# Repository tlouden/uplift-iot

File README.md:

# UPLIFT-IoT
Connecting an [UPLIFT](https://www.upliftdesk.com/) desk to Home Assistant using an ESP32 with ESP Home for Home Assistant.

## Disclaimer
This is an adversarial interop against a hardware interface. Any changes from the manufacturer could invalidate or even make this dangerous. Validate assumptions on your own system and proceed with caution. 

## Usage
The UART driver for ESP Home should work without modification. Everything else will need to be customized to your setup using the provided examples.

## ESP Home
An ESP32 is used with [ESP Home](https://esphome.io/). The specific board is a esp32doit-devkit-v1.
### esphome/uplift_uart.h
Custom UART driver that interprets the data from the UPLift desk unit.
### uplift-iot.yaml
An example definition for the device in ESPHome. Will need to be customized to be used.

## Home Assistant
Data is consumed by [Home Assistant](https://www.home-assistant.io/).
### homeassistant/automation.yaml 
An example automation which will need to be cusomized to be used.

## PCB / Board
[KiCAD](https://www.kicad.org/) files for a PCB are included for anyone that would like to produce their own. Here is the schematic if you'd like to breadboard it.

## Enclosure
[OpenSCAD](https://openscad.org/) files for an enclosure are included for 3D printing. The default values are good even if you use a header to connect the ESP to the board. Use M3x4mm screws to attach the PCB. The lid will snap fit. The [BOSL2 library](https://github.com/revarbat/BOSL2) is used and included along with it's license file.

## Details
### UPLIFT Wiring
On My UPLIFT Desk, the keypad communicates with the motor box via an ethernet cable. A logic analyser shows that the second wire has a digital signal at 9600 baud. The third wire is ground, and the fifth is a 5v supply. All the others get pulled low by the keypad when buttons are pressed.
### Signal Analysis
I don't want remote control of the motors, so my analysis is focused exlusively on the serial data on line 2. The data only sends few a short period after the desk height changes, then goes dead. This isn't a problem, but is good to know when doing analysis. Starting with defaults for parity, stop bits, and data length produced the data sequence 1, 1, [0,1], [0-255] repeating. The format is big endian, so the first integer is always 257 and the second is the real data. It is sending the height in tenths of an inch, so 296 is 29.6".
### UART Driver
A simple approach is used for such a simple use case. We look for the expected 1,1 data sequence and then process the next two bytes. It is possible to get out of sequence when the desk is higher than 25.5" so if the first byte is not a 0 or 1, the logic resets to avoid non-sensical readings like 1000". This allows up to 51.1" to be expressed, and my desk only goes up to 50.8".

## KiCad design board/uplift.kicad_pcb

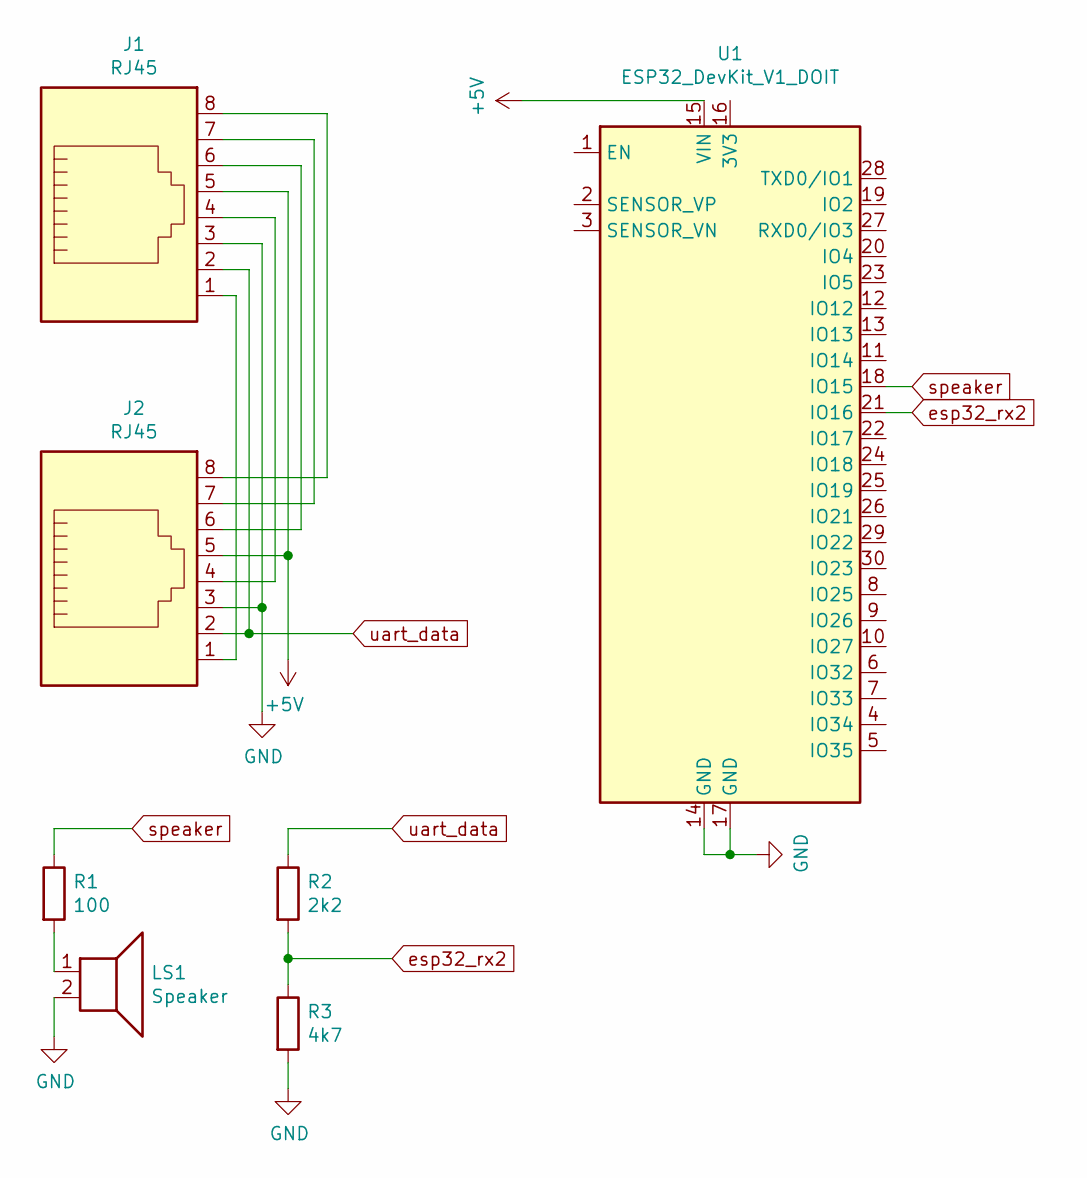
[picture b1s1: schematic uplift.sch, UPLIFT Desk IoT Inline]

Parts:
J1, J2: RJ45; RJ45_Amphenol_54602-x08_Horizontal
LS1: Speaker; MagneticBuzzer_ProSignal_ABT-410-RC
R1: 100; R_Axial_DIN0207_L6.3mm_D2.5mm_P10.16mm_Horizontal
R2: 2k2; R_Axial_DIN0207_L6.3mm_D2.5mm_P10.16mm_Horizontal
R3: 4k7; R_Axial_DIN0207_L6.3mm_D2.5mm_P10.16mm_Horizontal
U1: ESP32_DevKit_V1_DOIT; esp32_devkit_v1_doit

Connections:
+5V: J1.5, J2.5, U1.15 (VIN)
GND: J1.3, J2.3, LS1.2, R3.2, U1.14 (GND), U1.17 (GND)
unnamed: J1.1, J2.1
unnamed: J1.4, J2.4
unnamed: J1.6, J2.6
unnamed: J1.7, J2.7
unnamed: J1.8, J2.8
unnamed: LS1.1, R1.2
esp32_rx2: R2.2, R3.1, U1.21 (IO16)
speaker: R1.1, U1.18 (IO15)
uart_data: J1.2, J2.2, R2.1

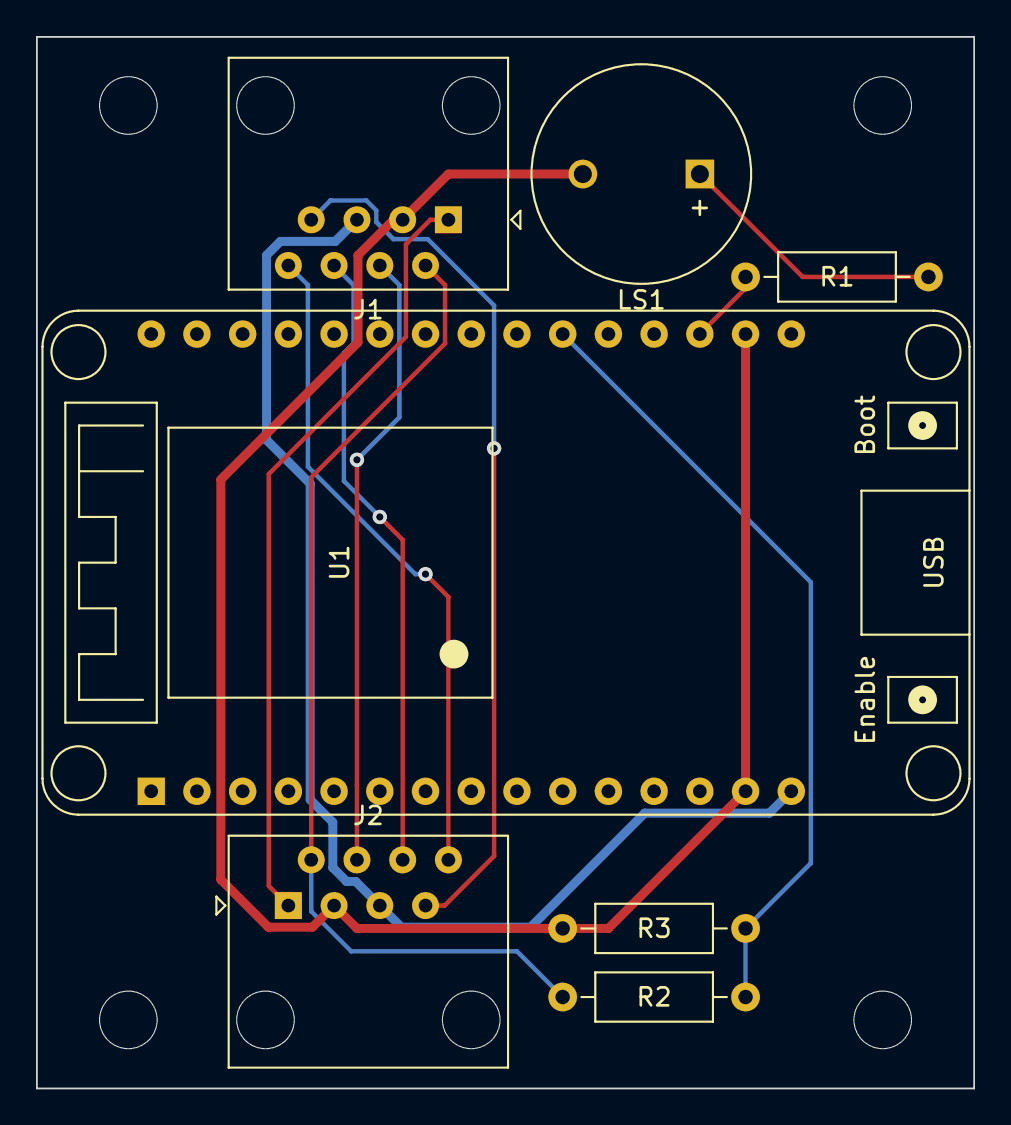
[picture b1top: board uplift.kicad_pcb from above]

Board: 2 copper layers, 52.1 x 58.4 mm, 7 parts (0 on the bottom side), 11 nets.

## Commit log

2021-09-20 combine c++ and kicad exclusions
2021-09-20 board, esphome, and home assistant files
2021-09-21 add enclosure files
2022-06-25 fix typos
